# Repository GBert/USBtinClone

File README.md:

USBtinClone
===========

This git contains hard- and software of a USBtin clone.
Original version:

http://www.fischl.de/usbtin/

This is a CAN2USB adapter which uses the SLCAN API. The SLCAN protocol doesn't
have the fastest API (all CAN frames are transfered into human readable ASCII),
but well known. Even Linux provides a kernel module for SocketCAN. 
The SLCAN API is also known as Lawicel protocol.

Difference to the orginal
-------------------------

The original version uses only through hole components which makes it easy to
solder. But the original version does have some little drawbacks IMHO.
So I started to make a clone:

- added galvanic isolation - no special hardware needed (eg TI ISO1050)
- fits into 5cm x 5cm square for cheap PCB
- one layer design for homebrew (only one brass jumper)

but still untested ...

Programming
-----------

First step is to programm the bootloader on the PIC18F14K50.
If you don't own a PIC programmer use a cheap USB cp2104
to flash the bootloader:

https://github.com/GBert/CP2104_GPIO

and then programm the usbtin code with:

http://code.google.com/p/mphidflash/

### Usage

```
modprobe can
modprobe can-raw
modprobe can-dev 
modprobe slcan
# configure 1Mbit  
slcand -o -s8 -S 3000000 ttyACM0 can0
 ifconfig -a
can0      Link encap:UNSPEC  Hardware Adresse 00-00-00-00-00-00-00-00-00-00-00-00-00-00-00-00  
          NOARP  MTU:16  Metrik:1
          RX packets:0 errors:0 dropped:0 overruns:0 frame:0
          TX packets:0 errors:0 dropped:0 overruns:0 carrier:0
          Kollisionen:0 Sendewarteschlangenlänge:10 
          RX-Bytes:0 (0.0 B)  TX-Bytes:0 (0.0 B)

ifconfig can0 up
ip -s -d link show can0
4: can0: <NOARP,UP,LOWER_UP> mtu 16 qdisc pfifo_fast state UNKNOWN mode DEFAULT qlen 10
    link/can 
    RX: bytes  packets  errors  dropped overrun mcast   
    0          0        0       0       0       0      
    TX: bytes  packets  errors  dropped carrier collsns 
    0          0        0       0       0       0     
```

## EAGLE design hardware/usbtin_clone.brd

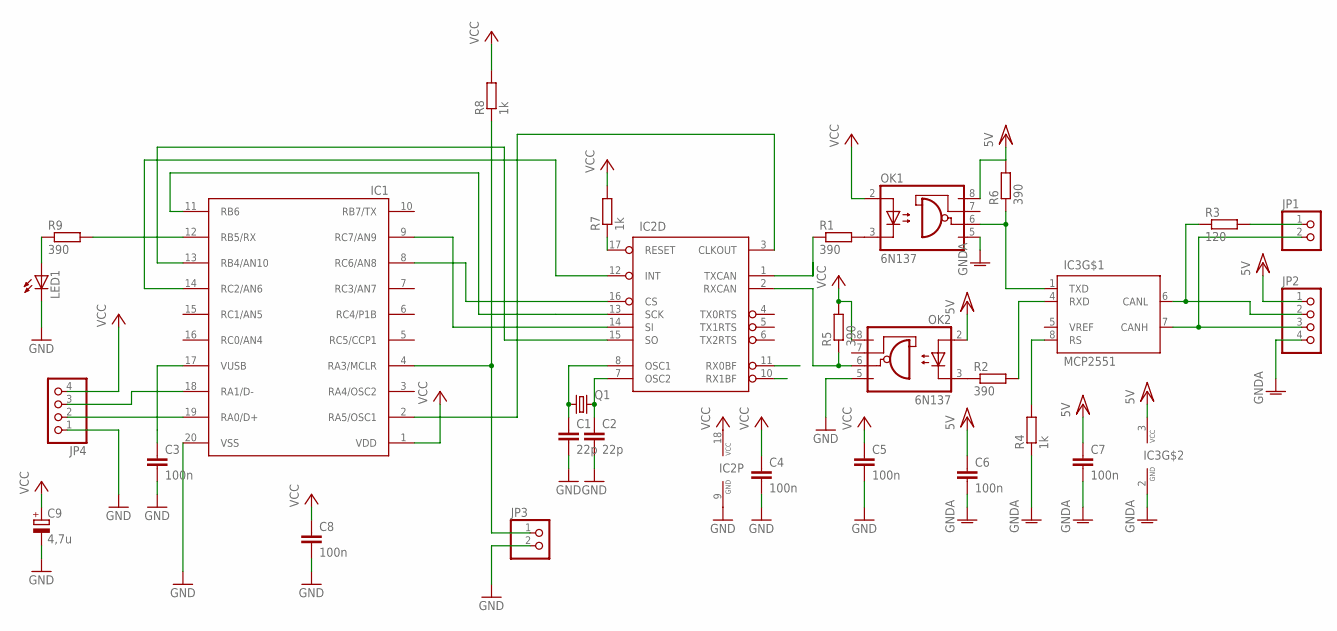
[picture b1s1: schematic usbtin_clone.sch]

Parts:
C1, C2: 22p; C025-025X050
C3, C4, C5, C6, C7, C8: 100n; C025-025X050
C9: 4,7u; E2,5-5
IC1: 18F14K50; DIL20
IC2: MCP2515P; DIL18
IC3: MCP2551; DIL08
JP1, JP3: PINHD-1X2; 1X02
JP2, JP4: PINHD-1X4; 1X04
LED1: LED3MM
OK1, OK2: 6N137; DIL08
Q1: CRYSTALHC49S; HC49/S
R1, R2, R5, R6, R9: 390; 0204/7
R3: 120; 0204/7
R4, R7, R8: 1k; 0204/7

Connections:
GND: C1.2, C2.2, C3.2, C4.2, C5.2, C8.2, C9.-, IC1.20 (VSS), IC2.9 (GND), JP3.2, JP4.1, LED1.K (C), OK2.5 (GND)
GNDA: C6.2, C7.2, IC3.2 (GND), JP2.4, OK1.5 (GND), R4.1
unnamed: C1.1, IC2.8 (OSC1), Q1.1
unnamed: C2.1, IC2.7 (OSC2), Q1.2
unnamed: OK1.3 (C), R1.2
unnamed: IC2.2 (RXCAN), OK2.6 (VO), R5.1
unnamed: IC2.1 (TXCAN), R1.1
unnamed: IC3.1 (TXD), OK1.6 (VO), R6.1
unnamed: OK2.3 (C), R2.1
unnamed: IC3.4 (RXD), R2.2
unnamed: IC3.6 (CANL), JP2.2, R3.1
unnamed: JP1.1, R3.2
unnamed: IC3.7 (CANH), JP1.2, JP2.3
unnamed: IC3.8 (RS), R4.2
unnamed: C3.1, IC1.17 (VUSB)
unnamed: IC2.17 (RESET), R7.1
unnamed: IC1.2 (RA5/OSC1), IC2.3 (CLKOUT)
unnamed: IC1.14 (RC2/AN6), IC2.12 (INT)
unnamed: IC1.4 (RA3/MCLR), JP3.1, R8.1
unnamed: IC1.19 (RA0/D+), JP4.2
unnamed: IC1.18 (RA1/D-), JP4.3
unnamed: IC1.12 (RB5/RX), R9.2
unnamed: LED1.A, R9.1
unnamed: IC1.8 (RC6/AN8), IC2.16 (CS)
unnamed: IC1.11 (RB6), IC2.13 (SCK)
unnamed: IC1.9 (RC7/AN9), IC2.14 (SI)
unnamed: IC1.13 (RB4/AN10), IC2.15 (SO)
VCC: C4.1, C5.1, C8.1, C9.+, IC1.1 (VDD), IC2.18 (VCC), JP4.4, OK1.2 (A), OK2.8 (VCC), R5.2, R7.2, R8.2
VCC/2: C6.1, C7.1, IC3.3 (VCC), JP2.1, OK1.8 (VCC), OK2.2 (A), R6.2

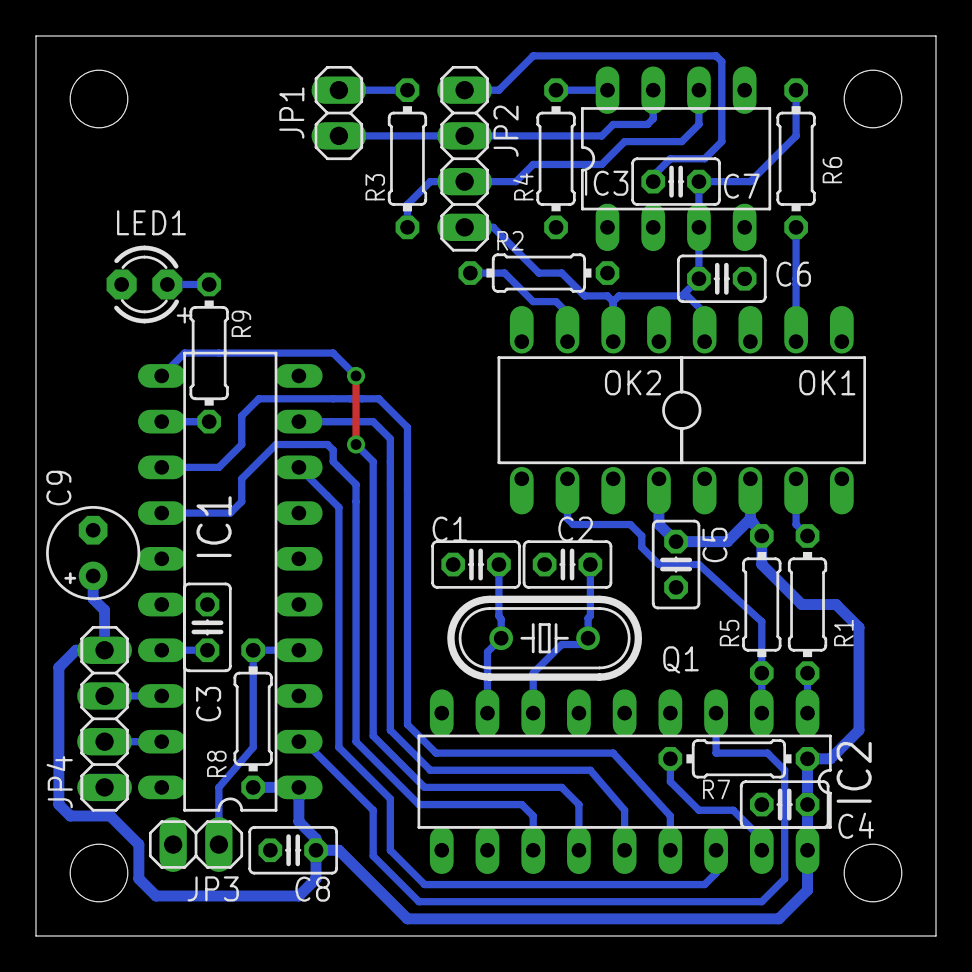
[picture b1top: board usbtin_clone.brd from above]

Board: 2 copper layers, 50.0 x 50.0 mm, 29 parts (0 on the bottom side), 29 nets.

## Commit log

2014-03-03 initial commit of Eagle design
2014-03-03 add some infos
2014-03-04 add copy script
2014-03-04 add text on bottom layer to identify mirroring
2014-03-04 add comment about diy mod to BRD file
2014-03-04 revert deleting
2014-03-04 minor BRD changes
2014-03-09 add vallues to schematic
2014-03-11 5V clearance
2014-03-11 show programmer
2014-03-11 add .k8048 defs
2014-03-11 clearify: Darrons k8048 programmer code is fast ...
2014-03-11 grr - CAN TX/RX fault
2014-04-01 correct bootloader programming -> use cp2104
2014-04-01 fix link
2014-04-01 add software from usbtin
2014-04-01 add link to flash the SLAN code
2014-04-01 fix typo
2014-04-02 add firmware for 64Byte bulk-transfer buffer
2014-04-06 add usb loader
